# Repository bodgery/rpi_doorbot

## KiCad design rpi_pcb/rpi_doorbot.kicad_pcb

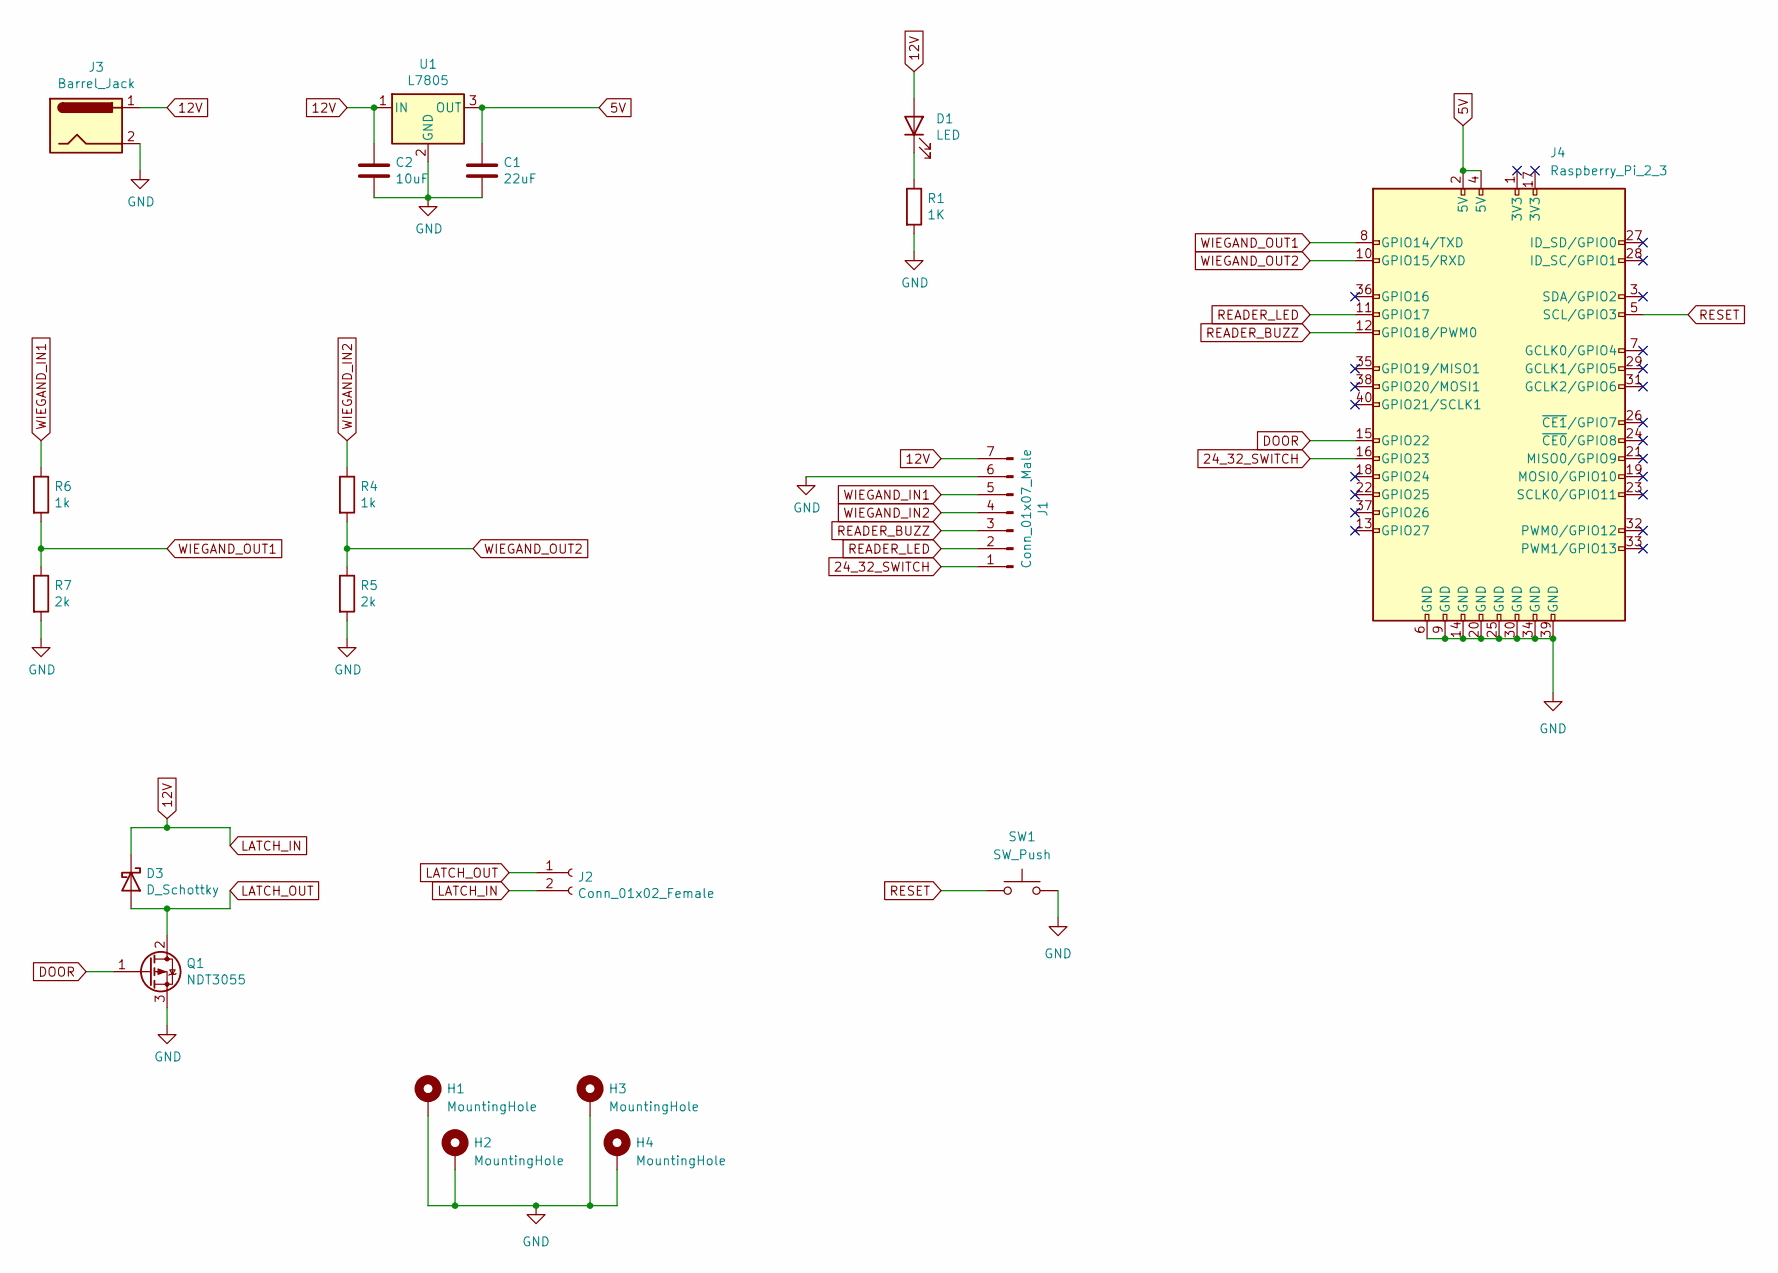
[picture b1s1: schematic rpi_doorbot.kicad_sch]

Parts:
C1: 22uF; C_1206_3216Metric; Digikey # 1276-1771-2-ND
C2: 10uF; C_1206_3216Metric; Digikey # 1276-6736-1-ND
D1: LED; LED_1206_3216Metric; Digikey # 1516-1073-2-N
D3: D_Schottky; D_1206_3216Metric; Digikey # 478-7805-2-ND
H1, H2, H3, H4: MountingHole; MountingHole_2.7mm_M2.5_Pad
J1: Conn_01x07_Male; Pin_Header_Straight_1x07
J2: Conn_01x02_Female; TerminalBlock_Pheonix_MKDS1.5-2pol; Digikey # ED2561-ND
J3: Barrel_Jack; TerminalBlock_Pheonix_MKDS1.5-2pol; Digikey # ED2561-ND
J4: Raspberry_Pi_2_3; PinHeader_2x20_P2.54mm_Vertical
Q1: NDT3055; SOT-223; Digikey # NDT3055CT-ND
R1: 1K; R_1210_3225Metric; Digikey # RMCF1210FT1K00
R4, R6: 1k; R_1210_3225Metric; Digikey # RMCF1210FT1K00
R5, R7: 2k; R_1210_3225Metric; Digikey # P2.0KVTR-ND
SW1: SW_Push; SW_SPST_PTS645; Digikey # CKN10880DKR-ND
U1: L7805; TO-220_Neutral123_Vertical; Digikey # 1470-VR10S05-ND

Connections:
5V: C1.1, J4.2 (5V), J4.4 (5V), U1.3 (OUT)
12V: C2.1, D1.2 (A), D3.1 (K), J1.7, J2.2, J3.1, U1.1 (IN)
24_32_SWITCH: J1.1, J4.16 (GPIO23)
DOOR: J4.15 (GPIO22), Q1.1 (G)
GND: C1.2, C2.2, H1.1, H2.1, H3.1, H4.1, J1.6, J3.2, J4.6 (GND), J4.9 (GND), J4.14 (GND), J4.20 (GND), J4.25 (GND), J4.30 (GND), J4.34 (GND), J4.39 (GND), Q1.3 (S), R1.2, R5.2, R7.2, SW1.2, U1.2 (GND)
LATCH_OUT: D3.2 (A), J2.1, Q1.2 (D)
unnamed: D1.1 (K), R1.1
READER_BUZZ: J1.3, J4.12 (GPIO18/PWM0)
READER_LED: J1.2, J4.11 (GPIO17)
RESET: J4.5 (SCL/GPIO3), SW1.1
WIEGAND_IN1: J1.5, R6.1
WIEGAND_IN2: J1.4, R4.1
WIEGAND_OUT1: J4.8 (GPIO14/TXD), R6.2, R7.1
WIEGAND_OUT2: J4.10 (GPIO15/RXD), R4.2, R5.1

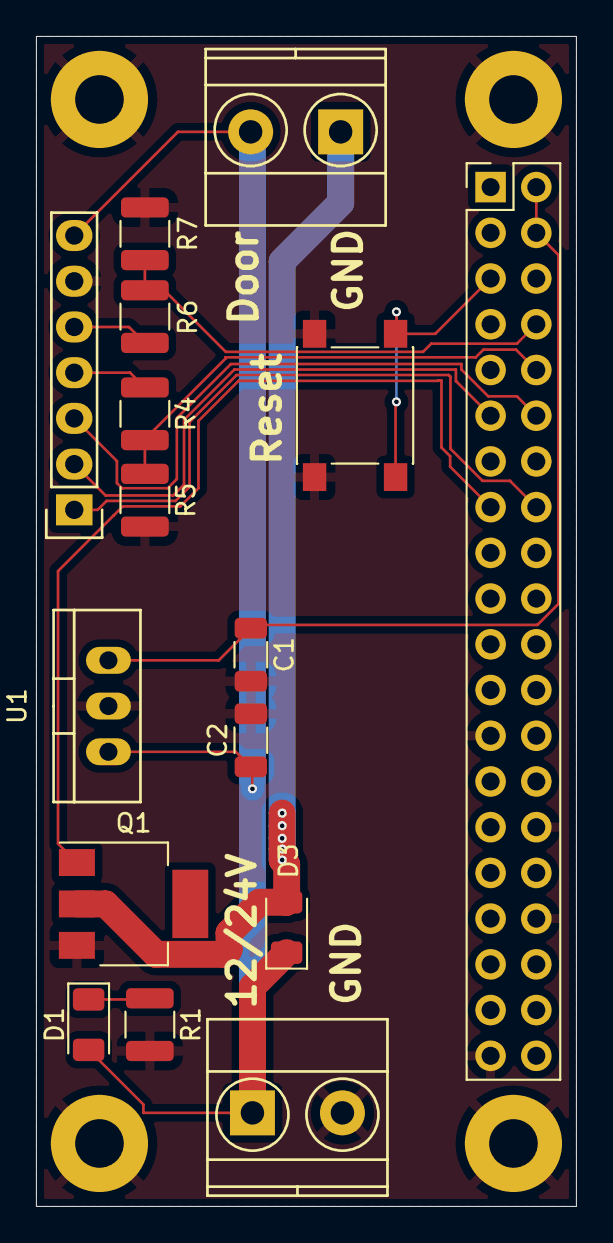
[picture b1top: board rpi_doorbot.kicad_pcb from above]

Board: 2 copper layers, 30.0 x 65.0 mm, 20 parts (0 on the bottom side), 14 nets.

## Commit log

2024-04-04 Initial import (from esp32_doorbot)
2024-04-05 RPi doorbot hat laid out
2024-04-05 Add readme

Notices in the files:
rpi_pcb/rpi_doorbot.kicad_pcb:
Copyright © 2024
